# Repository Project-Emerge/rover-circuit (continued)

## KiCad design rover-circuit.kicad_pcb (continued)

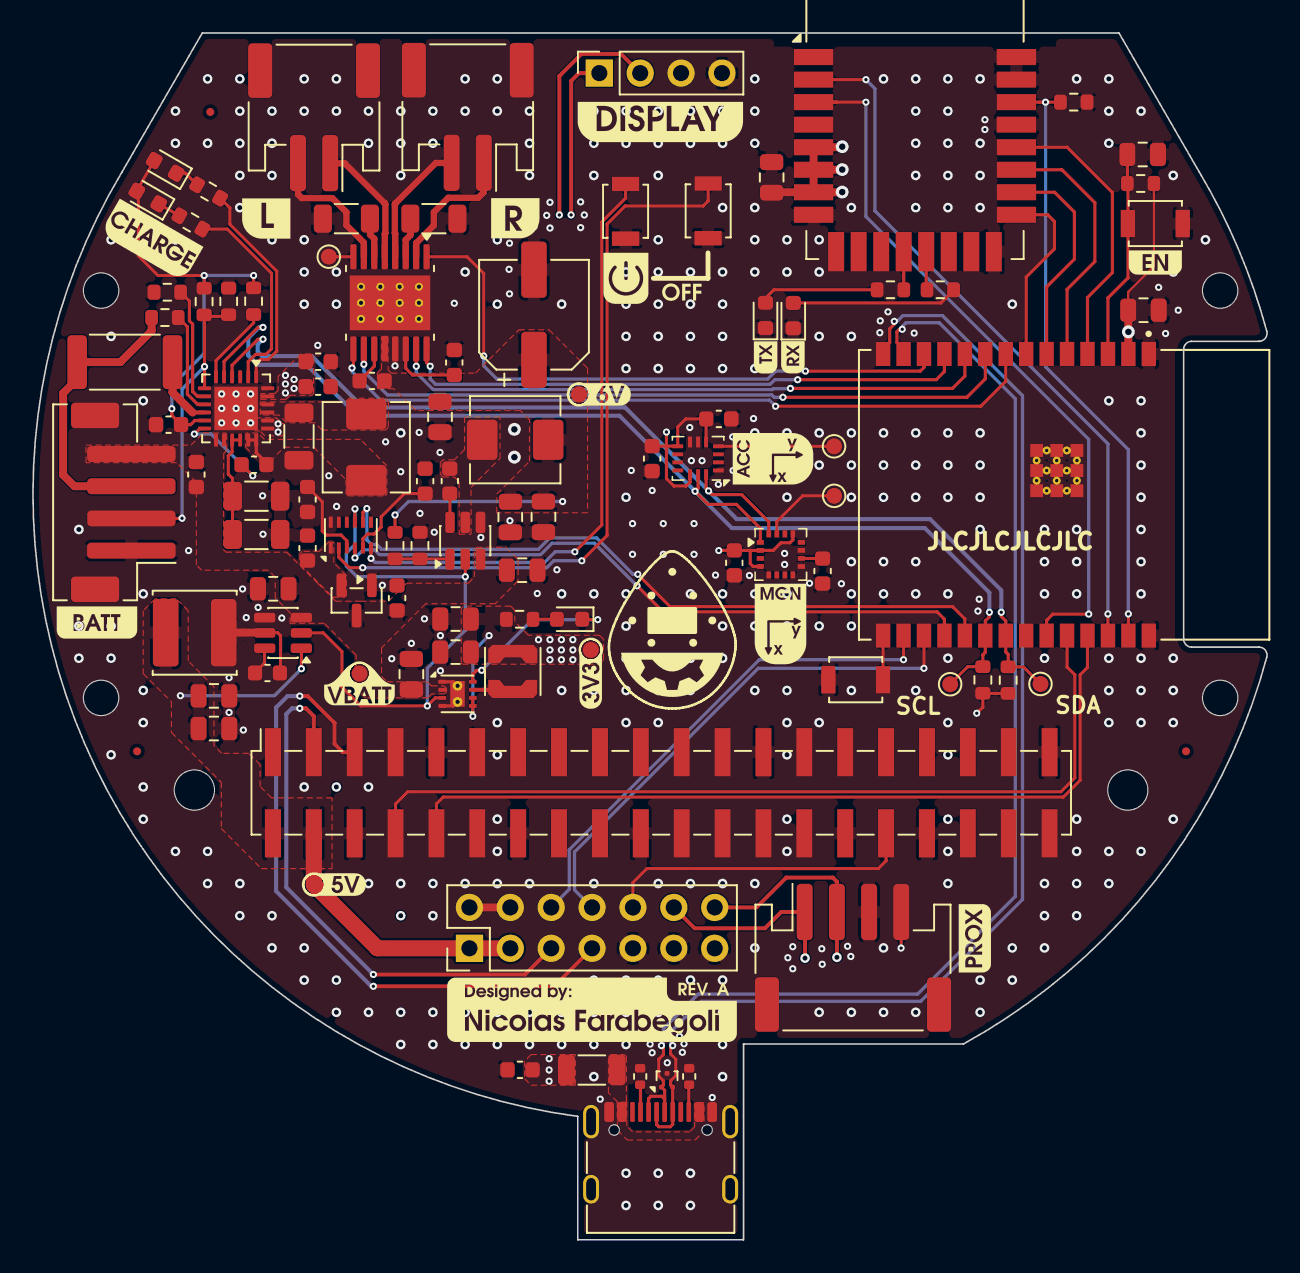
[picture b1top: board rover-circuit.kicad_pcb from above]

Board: 4 copper layers, 76.7 x 75.0 mm, 108 parts (0 on the bottom side), 81 nets.

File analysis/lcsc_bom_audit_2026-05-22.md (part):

# LCSC BOM audit - 2026-05-22

Target build quantity: 5 boards.
Estimated LCSC component spend from resolvable current selections: $94.69.
Validation counts: 57 ok, 2 review, 0 missing, 0 fail.

## Conservative updates generated

- None.

## Missing-part candidates


## Lines needing manual review

- DWM1: DWM1000 RF_Module:DWM1000 / C95238 - review: No current LCSC stock reported
- R5: 10 Resistor_SMD:R_2512_6332Metric / C1870255 - review: Package check needs review: footprint 2512, LCSC 

## Full table

| Refs | Value | Footprint | LCSC | Live MPN | Package | Stock | Buy qty | Unit USD | Status | Notes |
|---|---|---|---|---|---|---:|---:|---:|---|---|
| C1 | 100n | Capacitor_SMD:C_0805_2012Metric | C49678 | CC0805KRX7R9BB104 | 0805 | 15768009 | 5 | 0.004071 | ok | Exact LCSC code resolves to schematic MPN with matching package and stock |
| C3,C12 | 22uF | Capacitor_SMD:C_1206_3216Metric | C77091 | GRM31CR61E226KE15L | 1206 | 190767 | 10 | 0.081000 | ok | Exact LCSC code resolves to schematic MPN with matching package and stock |
| C4 | 47nF | Capacitor_SMD:C_0603_1608Metric | C1622 | CL10B473KB8NNNC | 0603 | 757584 | 5 | 0.004986 | ok | Exact LCSC code resolves to schematic MPN with matching package and stock |
| C5 | 10uF | Capacitor_SMD:C_1206_3216Metric | C13585 | CL31A106KBHNNNE | 1206 | 3941714 | 5 | 0.027714 | ok | Exact LCSC code resolves to schematic MPN with matching package and stock |
| C6 | 4.7uF | Capacitor_SMD:C_0603_1608Metric | C69335 | CL10A475KA8NQNC | 0603 | 872222 | 5 | 0.013743 | ok | Exact LCSC code resolves to schematic MPN with matching package and stock |
| C8 | 2.2uF | Capacitor_SMD:C_0603_1608Metric | C23630 | CL10A225KO8NNNC | 0603 | 5889919 | 5 | 0.005114 | ok | Exact LCSC code resolves to schematic MPN with matching package and stock |
| C9 | 10nF | Capacitor_SMD:C_0603_1608Metric | C1589 | CL10B103KB8NNNC | 0603 | 5951046 | 5 | 0.002971 | ok | Exact LCSC code resolves to schematic MPN with matching package and stock |
| C10 | 100uF | Capacitor_SMD:CP_Elec_6.3x5.4 | C2887276 | RVT100UF16V67RV0016 | SMD,D6.3xL5.4mm | 195109 | 5 | 0.026571 | ok | Exact LCSC code resolves to schematic MPN with matching package and stock |
| C11,C18,C25,C22 | 10uF | Capacitor_SMD:C_0805_2012Metric | C84416 | GRM21BR61E106KA73L | 0805 | 460193 | 20 | 0.016571 | ok | Exact LCSC code resolves to schematic MPN with matching package and stock |
| C15,C14,C7 | 10uF | Capacitor_SMD:C_0603_1608Metric | C962136 | CL10A106KO8NQNC | 0603 | 800663 | 15 | 0.025143 | ok | Exact LCSC code resolves to schematic MPN with matching package and stock |
| C16,C2,C26,C32 | 1uF | Capacitor_SMD:C_0603_1608Metric | C5673 | CL10A105KA8NNNC | 0603 | 1865987 | 20 | 0.003971 | ok | Exact LCSC code resolves to schematic MPN with matching package and stock |
| C21,C24,C20,C28,C23,C17 | 22uF | Capacitor_SMD:C_0805_2012Metric | C296720 | CL21A226KOQNNNE | 0805 | 318129 | 30 | 0.049000 | ok | Exact LCSC code resolves to schematic MPN with matching package and stock |
| C27 | 0.1uF | Capacitor_SMD:C_0805_2012Metric | C49678 | CC0805KRX7R9BB104 | 0805 | 15768009 | 5 | 0.004071 | ok | Exact LCSC code resolves to schematic MPN with matching package and stock |
| C30,C29,C13,C19 | 100nF | Capacitor_SMD:C_0603_1608Metric | C14663 | CC0603KRX7R9BB104 | 0603 | 81299425 | 20 | 0.002214 | ok | Exact LCSC code resolves to schematic MPN with matching package and stock |
| D1 | RED | LED_SMD:LED_0603_1608Metric | C2286 | KT-0603R | 0603 | 7824832 | 5 | 0.005314 | ok | Exact LCSC code resolves to schematic MPN with matching package and stock |
| D2 | GRN | LED_SMD:LED_0603_1608Metric | C965805 | XL-1608SYGC-06 | 0603 | 796384 | 5 | 0.006029 | ok | Exact LCSC code resolves to schematic MPN with matching package and stock |
| D3 | LED | LED_SMD:LED_0603_1608Metric | C2286 | KT-0603R | 0603 | 7824832 | 5 | 0.005314 | ok | Exact LCSC code resolves to schematic MPN with matching package and stock |
| D5,D6 | BLUE | LED_SMD:LED_0603_1608Metric | C965807 | XL-1608UBC-04 | 0603 | 1829633 | 10 | 0.003243 | ok | Exact LCSC code resolves to schematic MPN with matching package and stock |
| DWM1 | DWM1000 | RF_Module:DWM1000 | C95238 | DWM1000 |  | 0 | 5 |  | review | No current LCSC stock reported |
| J2 | USB_C_Receptacle_USB2.0_14P | Connector_USB:USB_C_Receptacle_G-Switch_GT-USB-7010ASV | C2988369 | GT-USB-7010ASV | SMD | 32723 | 5 | 0.074857 | ok | Exact LCSC code resolves to schematic MPN with matching package and stock |
| J3 | Conn_01x04 | Connector_PinSocket_2.54mm:PinSocket_1x04_P2.54mm_Vertical | C2718488 | 2.54-1*4P母 | 插件,P=2.54mm | 197666 | 5 | 0.043571 | ok | Package/value/stock checks pass from LCSC metadata |
| J4 | Conn_01x04_Socket | Connector_JST:JST_PH_S4B-PH-SM4-TB_1x04-1MP_P2.00mm_Horizontal | C265102 | S4B-PH-SM4-TB(LF)(SN) | SMD,P=2mm,卧贴 | 7 | 5 | 0.252571 | ok | Exact LCSC code resolves to schematic MPN with matching package and stock |
| J5 | Raspberry_Pi_2_3 | Connector_PinSocket_2.54mm:PinSocket_2x20_P2.54mm_Vertical_SMD | C22436166 | HC-PM254-8.5H-2x20PS | SMD,P=2.54mm | 224 | 5 | 0.475714 | ok | Exact LCSC code resolves to schematic MPN with matching package and stock |
| J6 | Conn_02x07_Odd_Even | Connector_PinHeader_2.54mm:PinHeader_2x07_P2.54mm_Vertical | C492424 | PZ254V-12-14P | 插件,P=2.54mm | 46071 | 5 | 0.071429 | ok | Exact LCSC code resolves to schematic MPN with matching package and stock |
| J7 | Right Motor | Connector_JST:JST_PH_S2B-PH-SM4-TB_1x02-1MP_P2.00mm_Horizontal | C295747 | S2B-PH-SM4-TB(LF)(SN) | SMD,P=2mm,卧贴 | 2800 | 5 | 0.193714 | ok | Exact LCSC code resolves to schematic MPN with matching package and stock |
| J8 | Left Motor | Connector_JST:JST_PH_S2B-PH-SM4-TB_1x02-1MP_P2.00mm_Horizontal | C295747 | S2B-PH-SM4-TB(LF)(SN) | SMD,P=2mm,卧贴 | 2800 | 5 | 0.193714 | ok | Exact LCSC code resolves to schematic MPN with matching package and stock |
| J9 | Battery Connector | Connector_JST:JST_PH_B4B-PH-SM4-TB_1x04-1MP_P2.00mm_Vertical | C160354 | B4B-PH-SM4-TB(LF)(SN) | SMD,P=2mm | 351847 | 5 | 0.166571 | ok | Exact LCSC code resolves to schematic MPN with matching package and stock |
| L1 | 1uH | Inductor_SMD:L_Sunlord_MWSA0518S | C167216 | FXL0630-1R0-M | SMD,7x6.6mm | 58187 | 5 | 0.095000 | ok | Exact LCSC code resolves to schematic MPN with matching package and stock |
| L2 | 2.2uH | Inductor_SMD:L_APV_ANR3012 | C2844756 | LPS3015-222MRC | SMD,3x3mm | 2011 | 5 | 0.642857 | ok | Exact LCSC code resolves to schematic MPN with matching package and stock |
| L3 | 4.7uH | Inductor_SMD:L_Sunlord_MWSA0503S | C108284 | LVS505040-4R7M-N | SMD,5x5mm | 1416 | 5 | 0.050429 | ok | Exact LCSC code resolves to schematic MPN with matching package and stock |
| L4 | 10uH | Inductor_SMD:L_Sunlord_MWSA0503S | C431344 | CMLW5040S100MST | SMD,5x5mm | 1430 | 5 | 0.061714 | ok | Exact LCSC code resolves to schematic MPN with matching package and stock |
| R1,R8 | 2.2k | Resistor_SMD:R_0603_1608Metric | C4190 | 0603WAF2201T5E | 0603 | 2960924 | 10 | 0.000914 | ok | Exact LCSC code resolves to schematic MPN with matching package and stock |
| R2 | 1.1K | Resistor_SMD:R_0603_1608Metric | C22764 | 0603WAF1101T5E | 0603 | 167734 | 5 | 0.000971 | ok | Exact LCSC code resolves to schematic MPN with matching package and stock |
| R3,R18,R12 | 10k | Resistor_SMD:R_0603_1608Metric | C2906982 | FRC0603F1002TS | 0603 | 8273747 | 15 | 0.000757 | ok | Exact LCSC code resolves to schematic MPN with matching package and stock |
| R4 | 300 | Resistor_SMD:R_0603_1608Metric | C2930092 | FRC0603F3000TS | 0603 | 275548 | 5 | 0.000871 | ok | Exact LCSC code resolves to schematic MPN with matching package and stock |
| R5 | 10 | Resistor_SMD:R_2512_6332Metric | C1870255 | CHP2512AFX-10R0ELF |  | 100 | 5 |  | review | Package check needs review: footprint 2512, LCSC  |
| R6 | 5.23k | Resistor_SMD:R_0603_1608Metric | C23068 | 0603WAF5231T5E | 0603 | 50706 | 5 | 0.001000 | ok | Exact LCSC code resolves to schematic MPN with matching package and stock |
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
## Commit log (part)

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2025-07-11 build: add gitignore
2025-07-11 build: exclude production files
2025-07-11 feat: add schematic and board layout
2025-07-11 ci: add CI/CD macinery
2025-07-12 fix: separate standby pins for motor drivers
2025-07-13 feat: use different 3v3 regulator
2025-07-14 ci: change workflow
2025-07-15 feat: change USB symbol and minor re-routing
2025-07-15 feat: suppress ERC warnings
2025-07-15 feat: suppress warnings in DRC
2025-07-15 ci: add release step
2025-07-15 ci: new action for release
2025-07-15 feat: re-route a trace
2025-08-09 Add renovate.json
2025-09-23 finalize components placement
2025-09-28 some updates
2025-09-29 add uwb module
2025-09-30 minors
2025-09-30 more on routing
2025-10-02 more routing
2025-10-03 some routing
2025-10-05 finalize routing
2025-10-06 complete routing
2026-03-16 Exclude tmp files
2026-03-16 start new design
2026-03-17 add recharger module
2026-04-02 update schematic
2026-04-05 ignore history folder
2026-04-05 add uwm and refactoring
2026-04-24 improve design
2026-04-24 change component code part
2026-04-24 Add LCSC part for esp32
2026-04-28 design pcb and place components
2026-05-01 moving on routing
2026-05-01 update PCB
2026-05-02 more on layout
2026-05-02 remove old files
2026-05-03 add 3d models
2026-05-03 some progress
2026-05-04 add components
2026-05-04 more on routing and schematic
2026-05-05 some improvements
2026-05-13 progress on routing
2026-05-15 try define requirements
2026-05-17 consolidated routing
2026-05-17 complete routing and validated ERC/DRC
2026-05-18 improved routing
2026-05-18 minor
2026-05-18 populated some components
2026-05-18 tentative automatic population
2026-05-20 Consistent final layout
2026-05-27 annotate with LCSC components
2026-05-27 changed power layout
2026-05-27 some optimizations
2026-05-28 optimized space
2026-05-28 finalized board
2026-05-28 cleanup
2026-05-30 finalized component selection
2026-05-30 add panelized version
2026-05-30 add jlcpcb components
2026-06-01 open hole in PCB under ESP32 for antenna
2026-06-01 oriented components
2026-06-05 improved layout
2026-06-30 add MPS entries
2026-06-30 update MPN codes
2026-06-30 fix: update OAR from 0.075 to 0.125 and regenerate panel & gerbers
